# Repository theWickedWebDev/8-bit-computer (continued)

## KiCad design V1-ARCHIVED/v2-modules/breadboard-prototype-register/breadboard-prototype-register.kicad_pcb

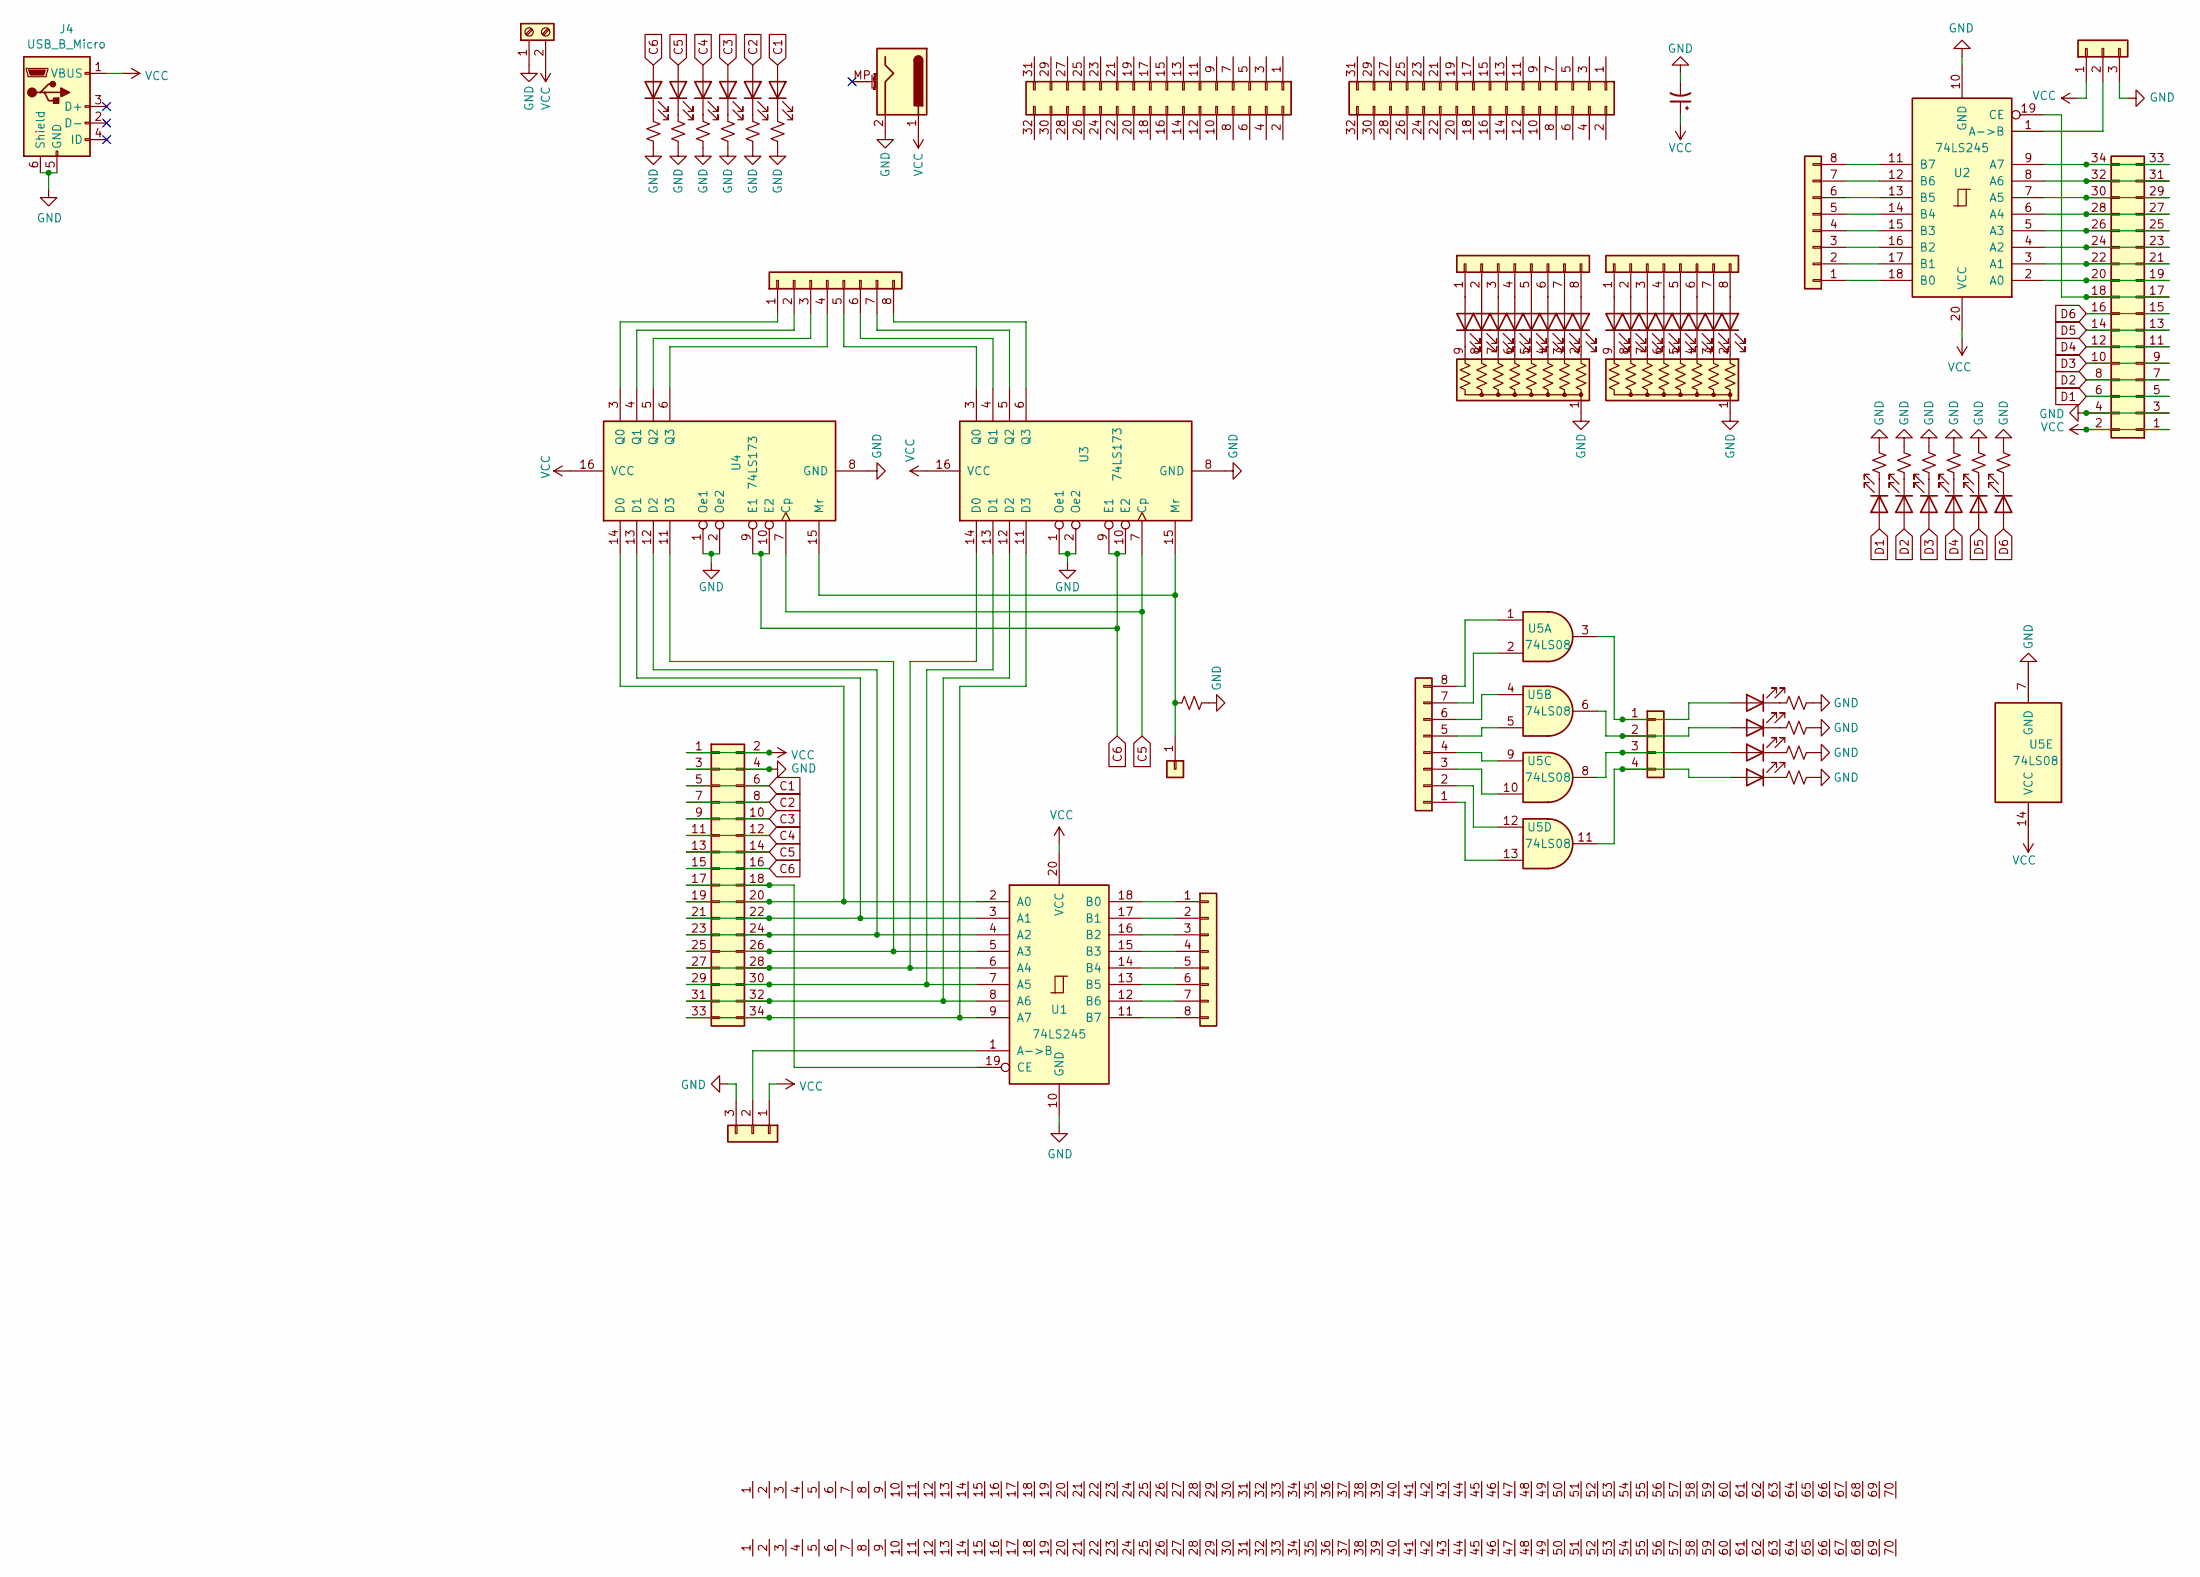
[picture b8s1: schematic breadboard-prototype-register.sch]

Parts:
C1: CP1_Small; CP_Radial_D8.0mm_P3.50mm
D1, D2, D3, D4, D5, D6, D7, D8, D9, D10, D11, D12, D13, D14, D15, D16: LED; LED_0805_2012Metric
D29, D30, D31, D32, D33, D34, D35, D36, D37, D38, D39, D40, D41, D42, D43, D44: LED; LED_D3.0mm
J1, J6: Conn_02x17_Odd_Even; PinHeader_2x17_P2.54mm_Vertical
J2, J7: Conn_01x03; PinHeader_1x03_P2.54mm_Vertical
J3, J8, J13, J15, J16, J19: Conn_01x08; PinHeader_1x08_P2.54mm_Vertical
J4: USB_B_Micro; USB_Micro-B_Wuerth_629105150521_CircularHoles
J5: Screw_Terminal_01x02; TerminalBlock_Phoenix_MKDS-1,5-2_1x02_P5.00mm_Horizontal
J9, J10: Conn_02x16_Odd_Even; connector_16_2
J11, J14: Conn_01x01; line_6x70
J12: Conn_01x01; PinHeader_1x01_P2.54mm_Vertical
J17: Barrel_Jack_MountingPin; BarrelJack_Horizontal
J18: Conn_01x04; PinHeader_1x04_P2.54mm_Vertical
R1, R2, R3, R4, R5, R6, R7, R8, R9, R10, R11, R12, R13, R14, R15, R16: R_Small_US; R_0805_2012Metric
R29: R_Small_US; R_Axial_DIN0309_L9.0mm_D3.2mm_P12.70mm_Horizontal
RN1, RN2: R_Network08_US; R_Array_SIP9
U1, U2: 74LS245; DIP-20_W7.62mm
U3, U4: 74LS173; DIP-16_W7.62mm
U5: 74LS08; DIP-14_W7.62mm

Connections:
C1: D1.2 (A), J1.5, J1.6
C2: D2.2 (A), J1.7, J1.8
C3: D3.2 (A), J1.9, J1.10
C4: D4.2 (A), J1.11, J1.12
C5: D5.2 (A), J1.13, J1.14, U3.7 (Cp), U4.7 (Cp)
C6: D6.2 (A), J1.15, J1.16, U3.9 (E1), U3.10 (E2), U4.9 (E1), U4.10 (E2)
D1: D12.2 (A), J6.5, J6.6
D2: D11.2 (A), J6.7, J6.8
D3: D10.2 (A), J6.9, J6.10
D4: D9.2 (A), J6.11, J6.12
D5: D8.2 (A), J6.13, J6.14
D6: D7.2 (A), J6.15, J6.16
GND: C1.2, J1.3, J1.4, J2.3, J4.5 (GND), J4.6 (Shield), J5.1, J6.3, J6.4, J7.3, J17.2, R1.2, R2.2, R3.2, R4.2, R5.2, R6.2, R7.2, R8.2, R9.2, R10.2, R11.2, R12.2, R13.2, R14.2, R15.2, R16.2, R29.2, RN1.1 (common), RN2.1 (common), U1.10 (GND), U2.10 (GND), U3.1 (Oe1), U3.2 (Oe2), U3.8 (GND), U4.1 (Oe1), U4.2 (Oe2), U4.8 (GND), U5.7 (GND)
unnamed: D1.1 (K), R1.1
unnamed: D2.1 (K), R2.1
unnamed: D3.1 (K), R3.1
unnamed: D4.1 (K), R4.1
unnamed: D5.1 (K), R5.1
unnamed: D6.1 (K), R6.1
unnamed: D7.1 (K), R9.1
unnamed: D8.1 (K), R10.1
unnamed: D9.1 (K), R11.1
unnamed: D10.1 (K), R12.1
unnamed: D11.1 (K), R13.1
unnamed: D12.1 (K), R14.1
unnamed: D13.1 (K), R7.1
unnamed: D13.2 (A), J18.1, U5.3
unnamed: D14.1 (K), R8.1
unnamed: D14.2 (A), J18.2, U5.6
unnamed: D15.1 (K), R15.1
unnamed: D15.2 (A), J18.3, U5.8
unnamed: D16.1 (K), R16.1
unnamed: D16.2 (A), J18.4, U5.11
unnamed: D29.1 (K), RN1.9 (R8)
unnamed: D29.2 (A), J15.1
unnamed: D30.1 (K), RN1.8 (R7)
unnamed: D30.2 (A), J15.2
unnamed: D31.1 (K), RN1.7 (R6)
unnamed: D31.2 (A), J15.3
unnamed: D32.1 (K), RN1.6 (R5)
unnamed: D32.2 (A), J15.4
unnamed: D33.1 (K), RN1.5 (R4)
unnamed: D33.2 (A), J15.5
unnamed: D34.1 (K), RN1.4 (R3)
unnamed: D34.2 (A), J15.6
unnamed: D35.1 (K), RN1.3 (R2)
unnamed: D35.2 (A), J15.7
unnamed: D36.1 (K), RN1.2 (R1)
unnamed: D36.2 (A), J15.8
unnamed: D37.1 (K), RN2.9 (R8)
unnamed: D37.2 (A), J16.1
unnamed: D38.1 (K), RN2.8 (R7)
unnamed: D38.2 (A), J16.2
unnamed: D39.1 (K), RN2.7 (R6)
unnamed: D39.2 (A), J16.3
unnamed: D40.1 (K), RN2.6 (R5)
unnamed: D40.2 (A), J16.4
unnamed: D41.1 (K), RN2.5 (R4)
unnamed: D41.2 (A), J16.5
unnamed: D42.1 (K), RN2.4 (R3)
unnamed: D42.2 (A), J16.6
unnamed: D43.1 (K), RN2.3 (R2)
unnamed: D43.2 (A), J16.7
unnamed: D44.1 (K), RN2.2 (R1)
unnamed: D44.2 (A), J16.8
unnamed: J1.17, J1.18, U1.19 (CE)
unnamed: J1.19, J1.20, U1.2 (A0), U4.14 (D0)
unnamed: J1.21, J1.22, U1.3 (A1), U4.13 (D1)
unnamed: J1.23, J1.24, U1.4 (A2), U4.12 (D2)
unnamed: J1.25, J1.26, U1.5 (A3), U4.11 (D3)
unnamed: J1.27, J1.28, U1.6 (A4), U3.14 (D0)
unnamed: J1.29, J1.30, U1.7 (A5), U3.13 (D1)
unnamed: J1.31, J1.32, U1.8 (A6), U3.12 (D2)
unnamed: J1.33, J1.34, U1.9 (A7), U3.11 (D3)
unnamed: J2.2, U1.1 (A->B)
unnamed: J3.1, U1.18 (B0)
unnamed: J3.2, U1.17 (B1)
unnamed: J3.3, U1.16 (B2)
unnamed: J3.4, U1.15 (B3)
unnamed: J3.5, U1.14 (B4)
unnamed: J3.6, U1.13 (B5)
unnamed: J3.7, U1.12 (B6)
unnamed: J3.8, U1.11 (B7)
unnamed: J6.17, J6.18, U2.19 (CE)
unnamed: J6.19, J6.20, U2.2 (A0)
unnamed: J6.21, J6.22, U2.3 (A1)
unnamed: J6.23, J6.24, U2.4 (A2)
unnamed: J6.25, J6.26, U2.5 (A3)
unnamed: J6.27, J6.28, U2.6 (A4)
unnamed: J6.29, J6.30, U2.7 (A5)
unnamed: J6.31, J6.32, U2.8 (A6)
unnamed: J6.33, J6.34, U2.9 (A7)
unnamed: J7.2, U2.1 (A->B)
unnamed: J8.1, U2.18 (B0)
unnamed: J8.2, U2.17 (B1)
unnamed: J8.3, U2.16 (B2)
unnamed: J8.4, U2.15 (B3)
unnamed: J8.5, U2.14 (B4)
unnamed: J8.6, U2.13 (B5)
unnamed: J8.7, U2.12 (B6)
unnamed: J8.8, U2.11 (B7)
unnamed: J12.1, R29.1, U3.15 (Mr), U4.15 (Mr)
unnamed: J13.1, U5.13
unnamed: J13.2, U5.12
unnamed: J13.3, U5.10
unnamed: J13.4, U5.9
unnamed: J13.5, U5.5
unnamed: J13.6, U5.4
unnamed: J13.7, U5.2
unnamed: J13.8, U5.1
unnamed: J19.1, U4.3 (Q0)
unnamed: J19.2, U4.4 (Q1)
unnamed: J19.3, U4.5 (Q2)
unnamed: J19.4, U4.6 (Q3)
unnamed: J19.5, U3.3 (Q0)
unnamed: J19.6, U3.4 (Q1)
unnamed: J19.7, U3.5 (Q2)
unnamed: J19.8, U3.6 (Q3)
VCC: C1.1, J1.1, J1.2, J2.1, J4.1 (VBUS), J5.2, J6.1, J6.2, J7.1, J17.1, U1.20 (VCC), U2.20 (VCC), U3.16 (VCC), U4.16 (VCC), U5.14 (VCC)

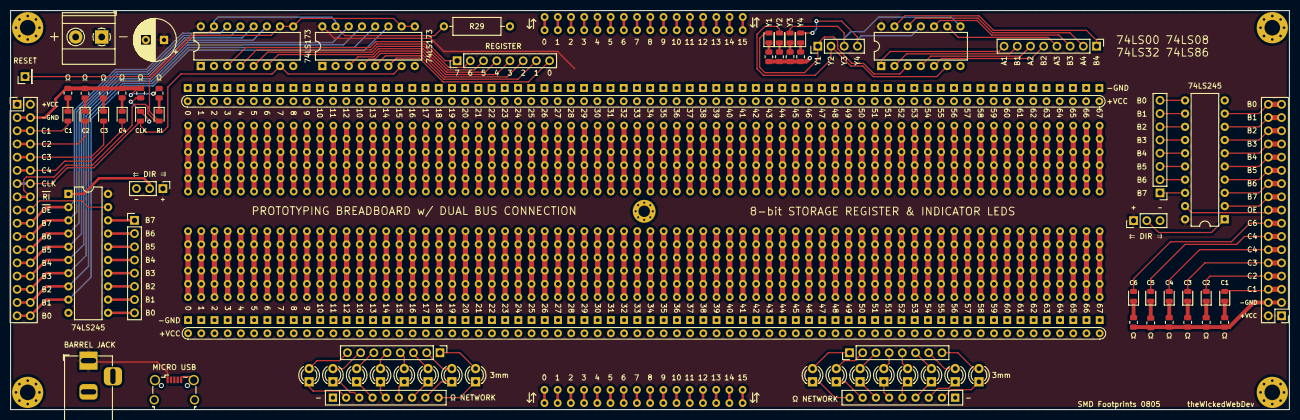
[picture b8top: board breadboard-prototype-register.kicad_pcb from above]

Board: 2 copper layers, 245.9 x 76.7 mm, 76 parts (0 on the bottom side), 119 nets.
